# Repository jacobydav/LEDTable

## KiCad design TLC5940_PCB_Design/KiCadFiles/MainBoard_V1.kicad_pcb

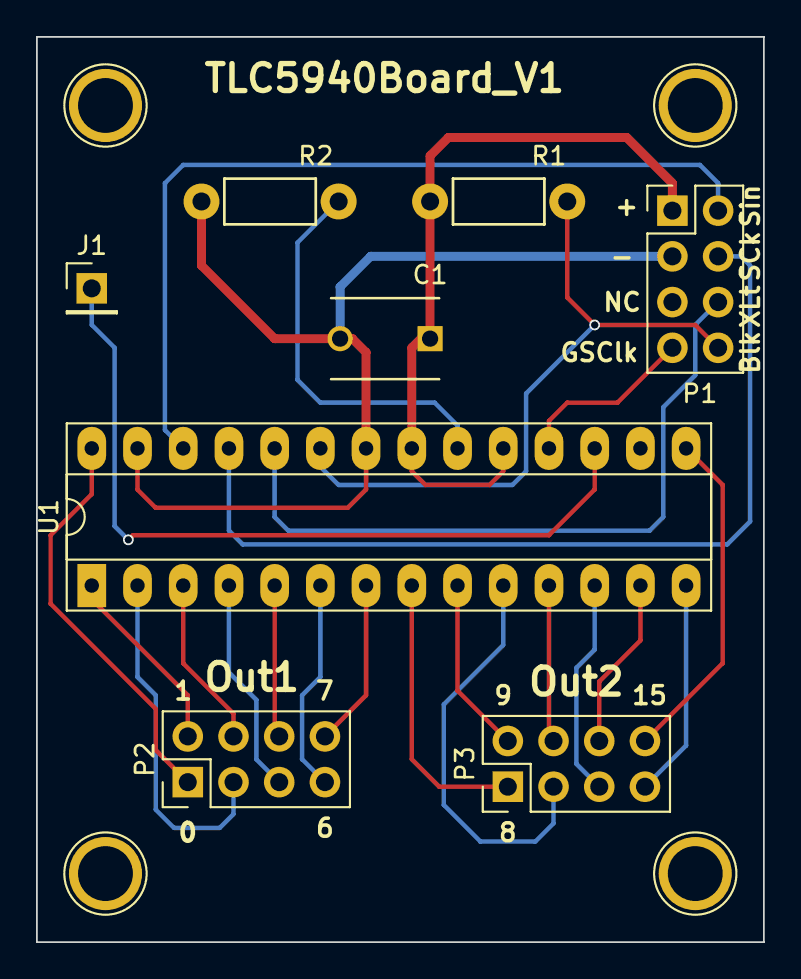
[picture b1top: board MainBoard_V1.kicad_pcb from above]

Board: 2 copper layers, 40.4 x 50.3 mm, 9 parts (0 on the bottom side), 25 nets.

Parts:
C1: 0.1uF; C_Disc_D6_P5
J1: SOut; Pin_Header_Straight_1x01_Pitch2.54mm
M1: 1pin
P1: CN_SigIn_02X04; Pin_Header_Straight_2x04_Pitch2.54mm
P2: CN_Out1_02X04; Pin_Header_Straight_2x04_Pitch2.54mm
P3: CN_Out2_02X04; Pin_Header_Straight_2x04_Pitch2.54mm
R1: 10K; Resistor_Horizontal_RM7mm
R2: 2K; Resistor_Horizontal_RM7mm
U1: TLC5940NT; DIP-28_W7.62mm_Socket_LongPads

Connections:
unnamed: C1.1, P1.1, R1.1, U1.19, U1.21
unnamed: C1.2, P1.3, R2.2, U1.22, U1.27
unnamed: J1.1, U1.17
unnamed: P1.2, U1.26
unnamed: P1.4, U1.25
unnamed: P1.6, U1.24
unnamed: P1.7, U1.18
unnamed: P1.8, R1.2, U1.23
unnamed: P2.1, U1.28
unnamed: P2.2, U1.1
unnamed: P2.3, U1.2
unnamed: P2.4, U1.3
unnamed: P2.5, U1.4
unnamed: P2.6, U1.5
unnamed: P2.7, U1.6
unnamed: P2.8, U1.7
unnamed: P3.1, U1.8
unnamed: P3.2, U1.9
unnamed: P3.3, U1.10
unnamed: P3.4, U1.11
unnamed: P3.5, U1.12
unnamed: P3.6, U1.13
unnamed: P3.7, U1.14
unnamed: P3.8, U1.15
unnamed: R2.1, U1.20

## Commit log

2017-04-22 :confetti_ball: Added .gitattributes & .gitignore files
2017-04-22 LED Table
    Project files for the beautiful table.
2017-04-27 Added Arduino code
2017-05-11 MSGEQ7 project, test pattern
    Added a test project for the LED flowers pattern
    Added the MSGEQ7 test project.
2017-05-22 Created the swirl pattern
2017-06-05 Drawings converted to pdf
2017-07-10 Updates for new version using tlc5947
    I changed to using 2 tlc5947 breakout boards to control the LEDs.
2017-08-20 Update to V3
    The new version using 2 TLC5947 boards. New LED patterns coded.
2017-09-24 Code and drawing updates
2018-01-13 Code updates
    Added a new pattern
